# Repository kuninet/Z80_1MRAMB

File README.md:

# Z80 128kB メモリーボード (KZ80-1MSRAM)

- 詳しい解説は以下のwikiページをご覧ください。

https://github.com/kuninet/Z80_1MRAMB/wiki

## 概要

- SBC8080ルーズキットバスにつながる128kBバンクメモリーボードです。
  - REV1 : 16kB ROM + 16kB固定RAM + 32kB 3バンクメモリー
  - REV2 ; 上記に加えて 64kBフルRAMモード装備
  - REV3 : ROM 32kジャンパ装備。アドレスデコード改良

## 機械語モニタ+TinyBASICについて

- [SBC8080データパック](http://www.amy.hi-ho.ne.jp/officetetsu/storage/sbc8080_datapack.zip)の機械語モニタ+TinyBASICを使用する場合、使用しているRAM領域(8000h〜FFFFh)をバンク切り替えする仕様となっているためRAMアドレス等を変更する必要があります。
  - [MON-TB](MON-TB/)ディレクトリにアドレス変更等を対応したソース/ROM焼き用のHEXファイルを添付しました。
  - https://github.com/kuninet/Z80_1MRAMB/tree/master/MON-TB

## ライセンス

- 本リポジトリのデータは MIT License のもとで公開します。[LICENSE.txt](LICENSE.txt)を参照して下さい。

## 参考リンク

- [SBC8080バスにつながる128kBメモリーボード(1)](https://kuninet.org/2018/08/11/sbc8080バスにつながる128kbメモリーボード1/)
- [SBC8080バスにつながる128kBメモリーボード(2)](https://kuninet.org/2018/08/12/sbc8080バスにつながる128kbメモリーボード2/)
- [SBC8080バスにつながる128kBメモリーボード(3)](https://kuninet.org/2018/08/13/sbc8080バスにつながる128kbメモリーボード3/)
  - 【注意】上記のBLOGの試作記事ではI/Oアドレスを40hにしていますが、当基板(REV1、1.1)では80hへ変更しています。
  
- KZ80-1MSRAM Rev.1 リリース0.9
  - [https://kuninet.org/2018/10/21/kz80-1msram-rev-1-%e3%83%aa%e3%83%aa%e3%83%bc%e3%82%b90-9/](https://kuninet.wordpress.com/2018/10/21/kz80-1msram-rev-1-%e3%83%aa%e3%83%aa%e3%83%bc%e3%82%b90-9/)
- KZ80/SBC80系 128kBメモリーボード REV2
  - [https://kuninet.org/2018/12/28/kz80-sbc80%e7%b3%bb-128kb%e3%83%a1%e3%83%a2%e3%83%aa%e3%83%bc%e3%83%9c%e3%83%bc%e3%83%89-rev2/](https://kuninet.wordpress.com/2018/12/28/kz80-sbc80%e7%b3%bb-128kb%e3%83%a1%e3%83%a2%e3%83%aa%e3%83%bc%e3%83%9c%e3%83%bc%e3%83%89-rev2/)

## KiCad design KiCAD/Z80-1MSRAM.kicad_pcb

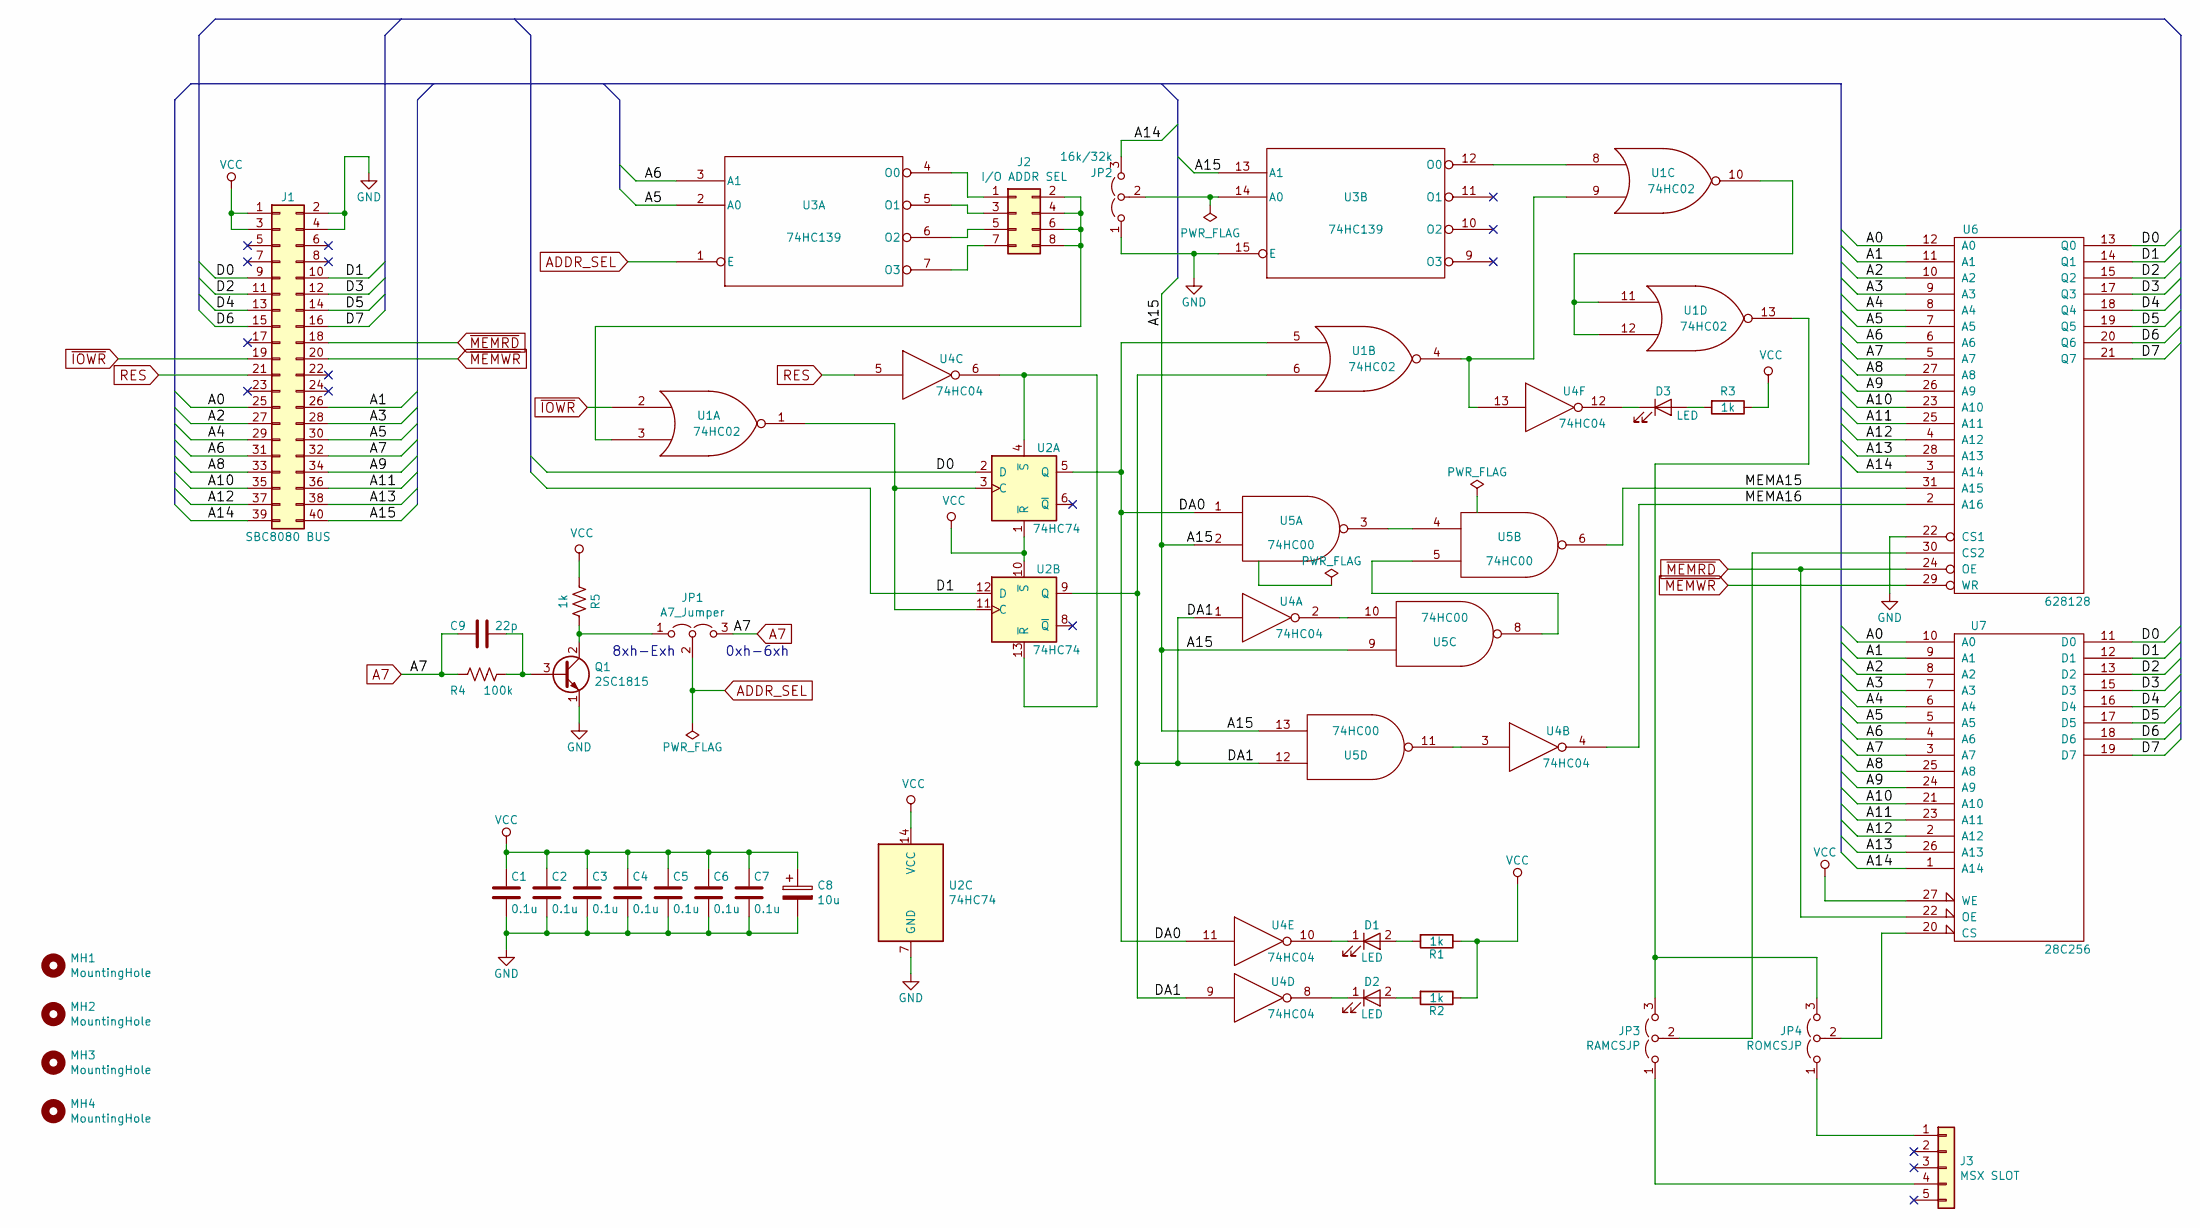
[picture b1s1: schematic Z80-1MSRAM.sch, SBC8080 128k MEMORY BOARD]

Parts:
C1, C2, C3, C4, C5, C6, C7: 0.1u; C_Rect_L4.0mm_W2.5mm_P2.50mm
C8: 10u; CP_Radial_D5.0mm_P2.50mm
C9: 22p; C_Disc_D3.0mm_W1.6mm_P2.50mm
D1, D2: LED; LED-3MM
D3: LED; LED_D3.0mm
J1: SBC8080 BUS; Pin_Header_Angled_2x20
J2: I/O ADDR SEL; PinHeader_2x04_P2.54mm_Vertical
J3: MSX SLOT; PinHeader_1x05_P2.54mm_Vertical
JP1: A7_Jumper; PinHeader_1x03_P2.54mm_Vertical
JP2: 16k/32k; PinHeader_1x03_P2.54mm_Vertical
JP3: RAMCSJP; PinHeader_1x03_P2.54mm_Vertical
JP4: ROMCSJP; PinHeader_1x03_P2.54mm_Vertical
MH1, MH2, MH3, MH4: MountingHole; MountingHole_3.2mm_M3
Q1: 2SC1815; TO-92L_Inline_Wide
R1, R2, R3, R5: 1k; R_Axial_DIN0207_L6.3mm_D2.5mm_P10.16mm_Horizontal
R4: 100k; R_Axial_DIN0207_L6.3mm_D2.5mm_P10.16mm_Horizontal
U1: 74HC02; DIP-14_W7.62mm_Socket
U2: 74HC74; DIP-14_W7.62mm_Socket
U3: 74HC139; DIP-16_W7.62mm_Socket
U4: 74HC04; DIP-14_W7.62mm_Socket
U5: 74HC00; DIP-14_W7.62mm_Socket
U6: 628128; DIP-32_W15.24mm_Socket
U7: 28C256; DIP-28_W15.24mm_Socket

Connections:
/A0: J1.25, U6.12 (A0), U7.10 (A0)
/A1: J1.26, U6.11 (A1), U7.9 (A1)
/A2: J1.27, U6.10 (A2), U7.8 (A2)
/A3: J1.28, U6.9 (A3), U7.7 (A3)
/A4: J1.29, U6.8 (A4), U7.6 (A4)
/A5: J1.30, U3.2 (A0), U6.7 (A5), U7.5 (A5)
/A6: J1.31, U3.3 (A1), U6.6 (A6), U7.4 (A6)
/A8: J1.33, U6.27 (A8), U7.25 (A8)
/A9: J1.34, U6.26 (A9), U7.24 (A9)
/A10: J1.35, U6.23 (A10), U7.21 (A10)
/A11: J1.36, U6.25 (A11), U7.23 (A11)
/A12: J1.37, U6.4 (A12), U7.2 (A12)
/A13: J1.38, U6.28 (A13), U7.26 (A13)
/A14: J1.39, JP2.3 (B), U6.3 (A14), U7.1 (A14)
/A15: J1.40, U3.13 (A1), U5.2, U5.9, U5.13
/D0: J1.9, U2.2 (D), U6.13 (Q0), U7.11 (D0)
/D1: J1.10, U2.12 (D), U6.14 (Q1), U7.12 (D1)
/D2: J1.11, U6.15 (Q2), U7.13 (D2)
/D3: J1.12, U6.17 (Q3), U7.15 (D3)
/D4: J1.13, U6.18 (Q4), U7.16 (D4)
/D5: J1.14, U6.19 (Q5), U7.17 (D5)
/D6: J1.15, U6.20 (Q6), U7.18 (D6)
/D7: J1.16, U6.21 (Q7), U7.19 (D7)
/DA0: U1.5, U2.5 (Q), U4.11, U5.1
/DA1: U1.6, U2.9 (Q), U4.1, U4.9, U5.12
/MEMA15: U5.6, U6.31 (A15)
/MEMA16: U4.4, U6.2 (A16)
A7: C9.2, J1.32, JP1.3 (B), R4.2, U6.5 (A7), U7.3 (A7)
ADDR_SEL: JP1.2 (C), U3.1 (E)
GND: C1.2, C2.2, C3.2, C4.2, C5.2, C6.2, C7.2, C8.2, J1.2, J1.4, JP2.1 (A), Q1.1 (E), U1.7 (GND), U2.7 (GND), U3.8 (GND), U3.15 (E), U4.7 (GND), U5.7 (GND), U6.16 (GND), U6.22 (CS1), U7.14 (GND)
unnamed: C9.1, Q1.3 (B), R4.1
unnamed: D1.1 (K), U4.10
unnamed: D1.2 (A), R1.2
unnamed: D2.1 (K), U4.8
unnamed: D2.2 (A), R2.2
unnamed: D3.1 (K), U4.12
unnamed: D3.2 (A), R3.2
unnamed: J2.1, U3.4 (O0)
unnamed: J2.2, J2.4, J2.6, J2.8, U1.3
unnamed: J2.3, U3.5 (O1)
unnamed: J2.5, U3.6 (O2)
unnamed: J2.7, U3.7 (O3)
unnamed: J3.1, JP4.1 (A)
unnamed: J3.4, JP3.1 (A)
unnamed: JP1.1 (A), Q1.2 (C), R5.1
unnamed: JP2.2 (C), U3.14 (A0)
unnamed: JP3.2 (C), U6.30 (CS2)
unnamed: JP3.3 (B), JP4.3 (B), U1.13
unnamed: JP4.2 (C), U7.20 (CS)
unnamed: U1.1, U2.3 (C), U2.11 (C)
unnamed: U1.4, U1.9, U4.13
unnamed: U1.8, U3.12 (O0)
unnamed: U1.10, U1.11, U1.12
unnamed: U2.4 (~S), U2.13 (~R), U4.6
unnamed: U4.2, U5.10
unnamed: U4.3, U5.11
unnamed: U5.3, U5.4
unnamed: U5.5, U5.8
RES: J1.21, U4.5
VCC: C1.1, C2.1, C3.1, C4.1, C5.1, C6.1, C7.1, C8.1, J1.1, J1.3, R1.1, R2.1, R3.1, R5.2, U1.14 (VCC), U2.1 (~R), U2.10 (~S), U2.14 (VCC), U3.16 (VCC), U4.14 (VCC), U5.14 (VCC), U6.32 (VCC), U7.27 (WE), U7.28 (VCC)
~IOWR: J1.19, U1.2
~MEMRD: J1.18, U6.24 (OE), U7.22 (OE)
~MEMWR: J1.20, U6.29 (WR)

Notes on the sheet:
0xh-6xh
8xh-Exh

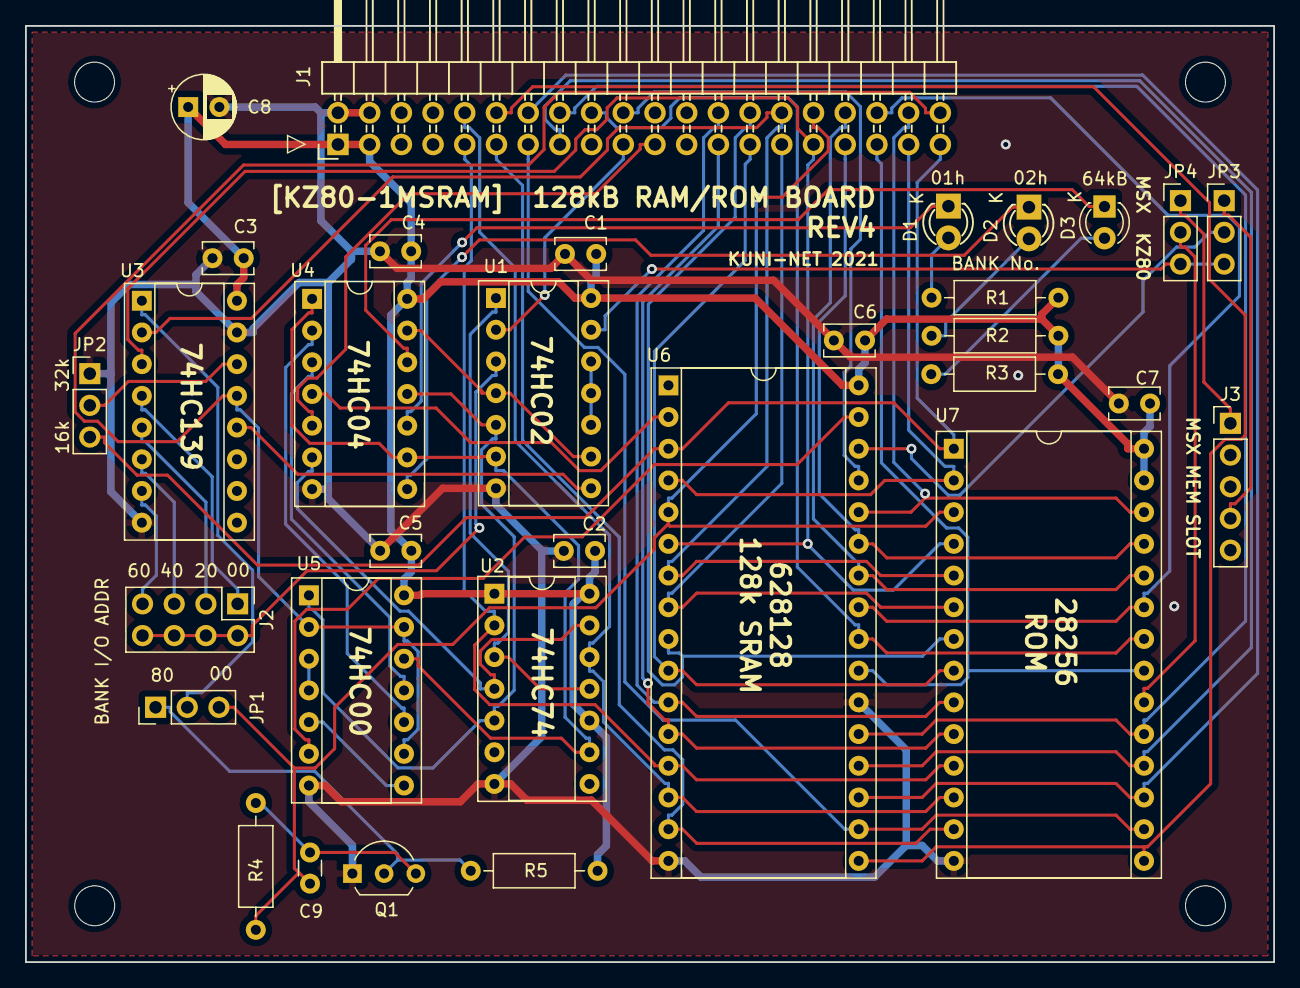
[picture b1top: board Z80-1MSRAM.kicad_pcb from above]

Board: 2 copper layers, 100.0 x 75.0 mm, 36 parts (0 on the bottom side), 63 nets.

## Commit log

2018-09-30 init commit
2018-10-07 KiCADデータ等整備
2018-10-07 git無視ファイル追加
2018-10-21 機械語モニタ+TinyBASIC アドレス変更版ソース追加
2018-10-22 電源部へコンデンサ追加&パターン調整
2018-11-18 Rev1.1パターン見直し
2018-11-18 回路図更新
2018-11-18 部品表更新
2018-11-18 部品表誤記修正
2018-12-06 REV2基板対応
2019-01-10 シルクパターン等整備
2019-03-14 REV3 基板関係 試作バージョン
2019-03-17 REV3からREV2.1へ改名 回路図 & 製造データ出力
2019-03-17 旧回路図(REV2)別ファイルへ
2019-09-07 REV3 回路図、プリントパターン、ガーバーデータ
2019-09-08 REV1回路図復活。REV3回路図改名
2021-03-24 REV4基板 ガーバーデータ出力
2021-03-24 REV4 基板 部品配置変更・ガーバー出力
2021-03-25 基板パターン 縁から離す対応・ガーバー出力
2021-03-25 パターン微調整
